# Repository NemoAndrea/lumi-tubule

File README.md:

> **warning** 🚧 Under Construction - There is still a lot of work to be done on this project. Have a look at issues if you want to contribute (e.g. review PCB) or check back later when the project is getting closer to release 👷

## LumiTubule - open hardware decorative led sculpture

LumiTubule is a simple decorative lamp in the shape of a [microtubule]() that can be programmed to respond to events (e.g. emails). While primarily decorative, the PCB comes with a temperature and humidity sensor and a basic accelerometer for user interaction - and a stemma QT port in case you want to add more sensors!

It's all powered by a small USB-C power supply, so it barely takes up any desk space.

The PCB design, 3D printable files and bill of materials are all available, so you can put together your own LumiTubule. If you would like to have one, but would rather not go through the assembly process, you can get in touch. 

### Components

There are 4 key components that make up the LumiTubule

1. The custom PCB with ESP32 microcontroller and onboard sensors
2. A [15W USB-C power supply](https://www.raspberrypi.com/products/type-c-power-supply/)
3. The 3D printed microtubule sculpture (translucent)
4. The 13 flexible LED filaments that sit inside the sculpture

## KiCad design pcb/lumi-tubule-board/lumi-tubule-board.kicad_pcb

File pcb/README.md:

### LumiTubule PCB

The LumiTubule PCB is generated with KiCad 6.0

The following plugins were used:

* [Teardrops plugin](https://github.com/NilujePerchut/kicad_scripts/tree/master/teardrops) (manual install - in PCBnew go to `tools` > `external plugins` > `open plugin directory`) 
* [Rounded tracks plugin](https://github.com/mitxela/kicad-round-tracks) (via plugin manager)

### Graphics

The graphics for the board are primarily created in Affinity Designer, with the help of [Inkscape](https://inkscape.org/) for some of the outline traces and image binarisation.

Some weird quirks during drawing process

- KiCad seems really picky about when it will render the hole in the board. The outline of the board has a lot of polygons. I am not sure what property of the inner circle makes it work better, but be aware that some frustrations may occur here if you try to change it.

### Considerations

> **Note** The points below provide some insight into why certain parts were selected. If you spot any errors in the calculations or reasoning, feel free to let me know!

**LED filament current setting resistor value `R_ext`**

The LED filaments can handle about 100mA current (more in practice seems fine), so let's aim for that value. We need to chose `R_ext` for the `TLC59108` and find an internal configuration to match. 

We look [in the datasheet](https://www.ti.com/lit/ds/symlink/tlc59108.pdf) and glance at section `10.1.1.2` ('adjusting the output current') . We see that the output current will depend on `R_ext`, `VG`, and `CM`. The latter two are configurable via internal register `IREF`. The default value of `CM` is 1, which sets `I_out/I_ref` = 15, and is listed as suitable for the 10mA-120mA regime; so we do not need to adjust this.   

`VG` is a more complicated value, being composed of the internal register value `HC` and `CC[5:0]`. Its default value is ~1 (0.992), which means that `V_ext` =1.25V (which has the following dependence: `V_ext = 1.26 * VG`).

Now we can put it together. We want `I_out`=100mA, so we need `I_ext` to be 100/15= 6.67mA. `I_ext` is simply set by `V_ext/R_ext`. So we need `R_ext` = 1.25/( 6.67 E-3) = **187.4 Ohm**. Dissipation in this resistor will only be (6.67mA)^2 * 187 = 10mW, so we can pretty much pick any package size.

### Generating fabrication outputs

We can generate a BOM from the schematic editor. We use a slightly modified version of [this custom script](https://gist.githubusercontent.com/arturo182/a8c4a4b96907cfccf616a1edb59d0389/raw/2c9191c0f1fe5471db3362ccf29f71d3235af4d4/bom2grouped_csv_jlcpcb.xsl) where we fetch part numbers from the custom field name 'JLCPCB ref' instead. You can see the value of this field in the schematic editor for each component. This is based on advice [from JLCPCB](https://support.jlcpcb.com/article/84-how-to-generate-the-bom-and-centroid-file-from-kicad).

We then turn to the PCB editor. We first need to run the [Rounded tracks plugin](https://github.com/mitxela/kicad-round-tracks). Run it with default parameters, and make sure you generate a new file. 

Next up, run the [Teardrops plugin](https://github.com/NilujePerchut/kicad_scripts/tree/master/teardrops). Use the following settings.

Now we can generate the `.gbr` files. We do this following [the suggestions by JLCPCB](https://support.jlcpcb.com/article/194-how-to-generate-gerber-and-drill-files-in-kicad-6). **In addition, we need to tick the place file origin option, as the PCB uses a virtual origin.** In short:

And for the drill file (we want to again pick the `drill/place file` origin:

Finally we need to generate the placement file. This is done from the PCB editor under `fabrication outputs`. We generate a `.pos` file. Per [instructions from JLCPCB](https://support.jlcpcb.com/article/84-how-to-generate-the-bom-and-centroid-file-from-kicad) we start with these settings in `KiCad`:

And then in the resulting `.csv` we change the following bits:

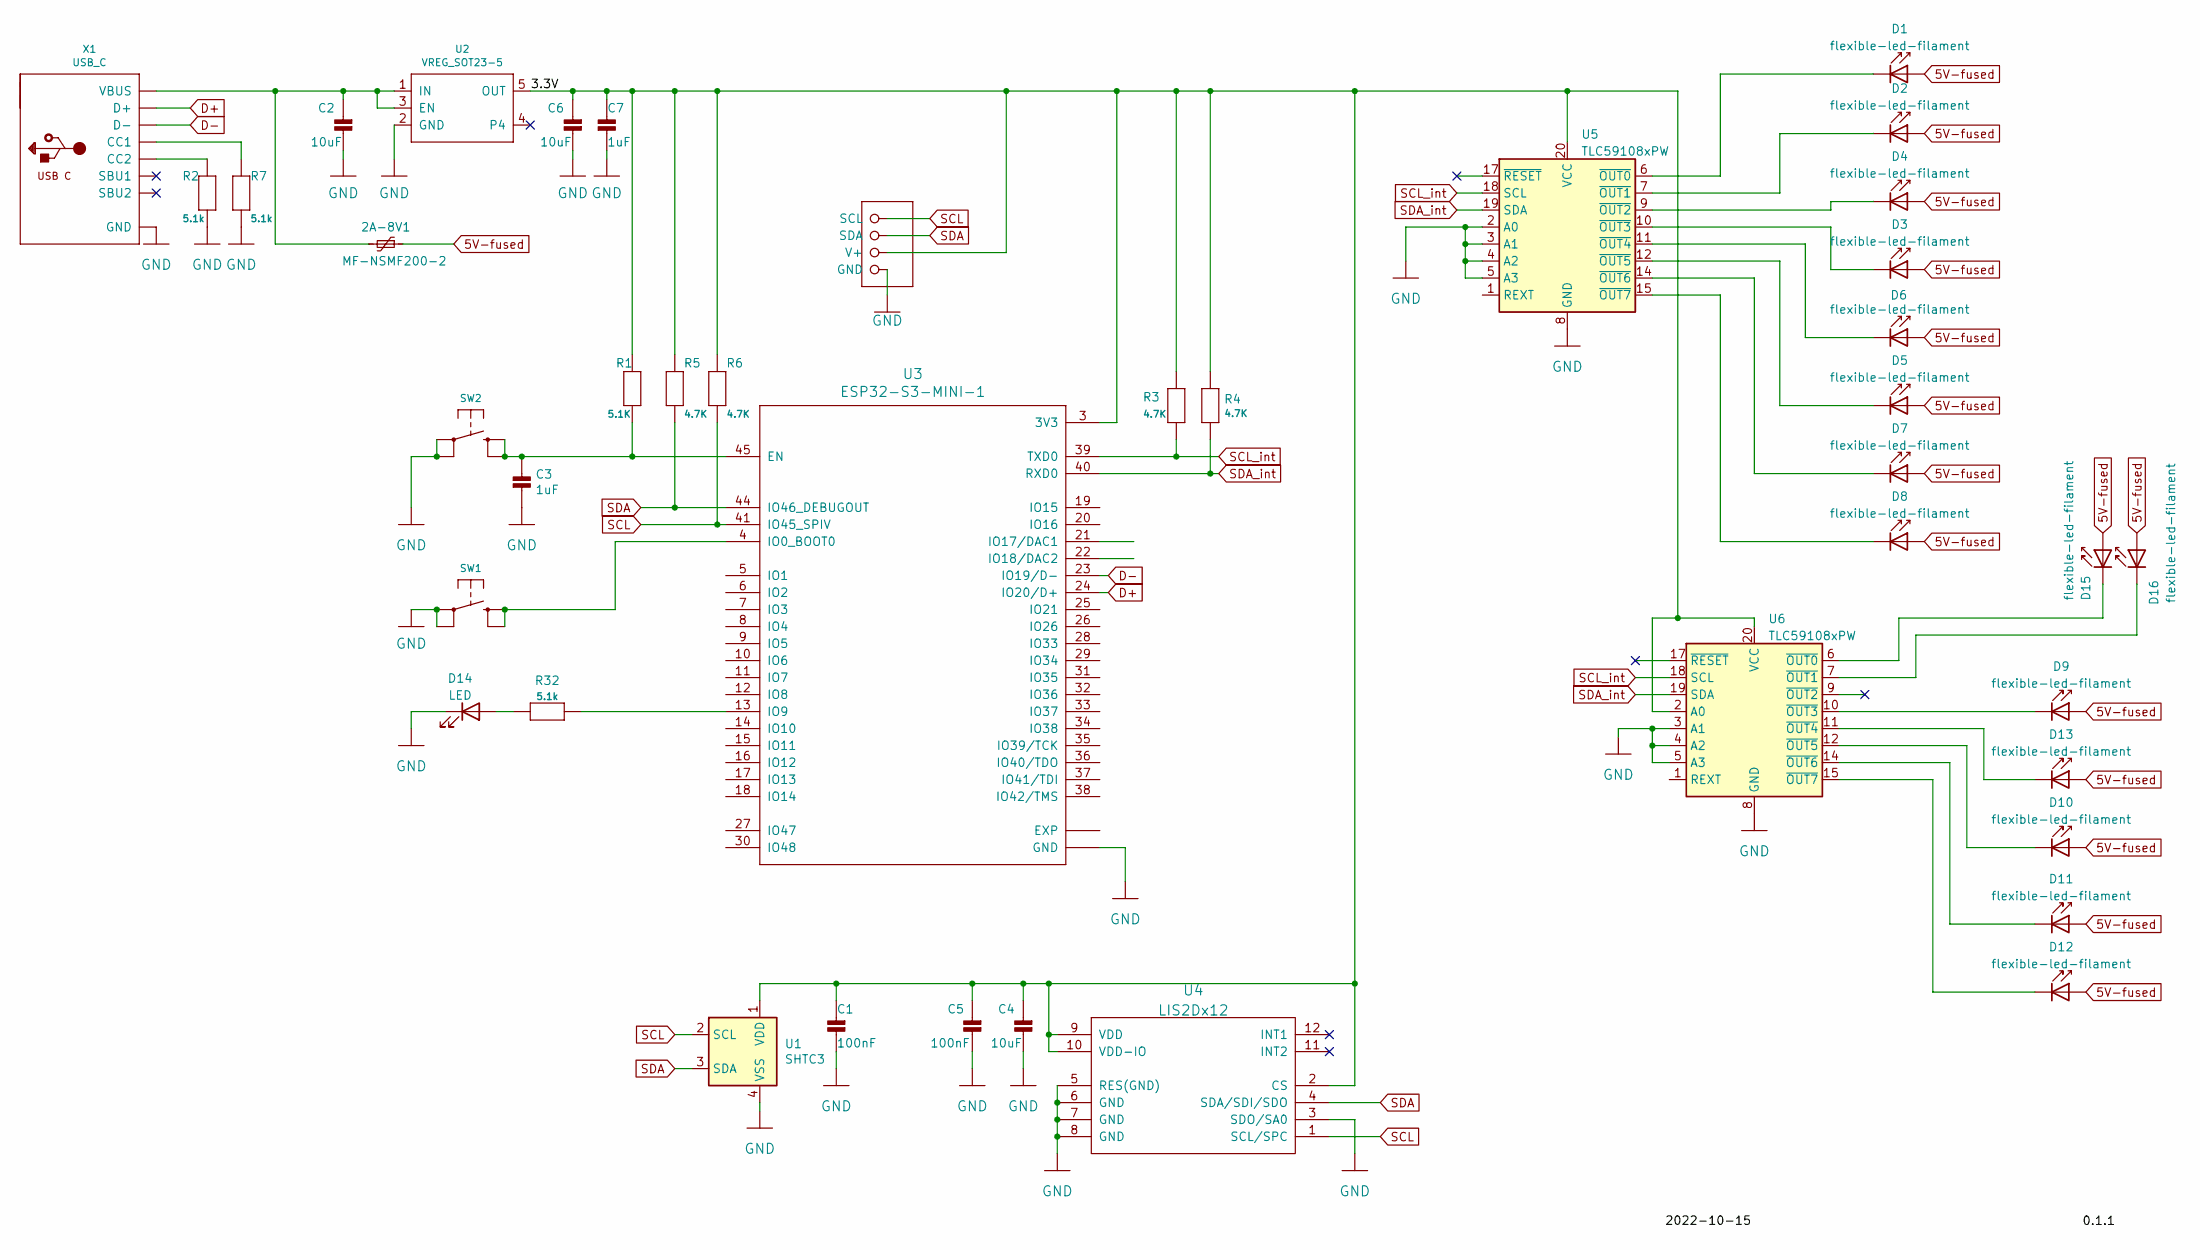
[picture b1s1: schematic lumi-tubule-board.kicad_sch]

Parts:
2A-8V1: MF-NSMF200-2
C1, C5: 100nF; C_0402_1005Metric; JLCPCB ref C307331
C2, C4, C6: 10uF; C_0805_2012Metric; JLCPCB ref C440198
C3, C7: 1uF; C_0603_1608Metric; JLCPCB ref C15849
CONN1: STEMMA_I2C_QTSKINNY; JST_SH_BM04B-SRSS-TB_1x04-1MP_P1.00mm_Vertical; JLCPCB ref C160390
D1, D2, D3, D4, D5, D6, D7, D8, D9, D10, D11, D12, D13, D15, D16: flexible-led-filament; Flexible LED filament viamount
D14: LED; LED_0603_1608Metric; JLCPCB ref C72043
R1: 5.1K; R_0805_2012Metric
R2, R7, R32: 5.1k; R_0603_1608Metric; JLCPCB ref C22961
R3, R4, R5, R6: 4.7K; R_0603_1608Metric; JLCPCB ref C23162
SW1, SW2: SWITCH_TACT_SMT4.6X2.8; BTN_KMR2_4.6X2.8
U1: SHTC3; Sensirion_DFN-4-1EP_2x2mm_P1mm_EP0.7x1.6mm; JLCPCB ref C194656
U2: VREG_SOT23-5; SOT-23-5; JLCPCB ref C176944
U3: ESP32-S3-MINI-1; ESP32-S2-MINI-1; JLCPCB ref C2913206
U4: LIS2Dx12; LGA-12_2x2mm_P0.5mm; JLCPCB ref C110926
U5, U6: TLC59108xPW; TSSOP-20_4.4x6.5mm_P0.65mm
X1: USB_C; USB_C_Receptacle_HRO_TYPE-C-31-M-12

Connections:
5V-fused: 2A-8V1.1, D1.2 (A), D2.2 (A), D3.2 (A), D4.2 (A), D5.2 (A), D6.2 (A), D7.2 (A), D8.2 (A), D9.2 (A), D10.2 (A), D11.2 (A), D12.2 (A), D13.2 (A), D15.2 (A), D16.2 (A)
/3.3V: C1.2, C4.2, C5.2, C6.2, C7.1, CONN1.2 (V+), R1.1, R3.1, R4.1, R5.1, R6.1, U1.1 (VDD), U2.5 (OUT), U3.3 (3V3), U4.2 (CS), U4.9 (VDD), U4.10 (VDD-IO), U5.20 (VCC), U6.2 (A0), U6.20 (VCC)
D+: U3.24 (IO20/D+), X1.A6 (D+), X1.B6 (D+)
D-: U3.23 (IO19/D-), X1.A7 (D-), X1.B7 (D-)
unnamed: 2A-8V1.2, C2.2, U2.1 (IN), U2.3 (EN), X1.A4 (VBUS), X1.A9 (VBUS), X1.B4 (VBUS), X1.B9 (VBUS)
unnamed: C3.1, R1.2, SW2.B (S), SW2.B' (S1), U3.45 (EN)
unnamed: D1.1 (K), U5.6 (~OUT0)
unnamed: D2.1 (K), U5.7 (~OUT1)
unnamed: D3.1 (K), U5.10 (~OUT3)
unnamed: D4.1 (K), U5.9 (~OUT2)
unnamed: D5.1 (K), U5.12 (~OUT5)
unnamed: D6.1 (K), U5.11 (~OUT4)
unnamed: D7.1 (K), U5.14 (~OUT6)
unnamed: D8.1 (K), U5.15 (~OUT7)
unnamed: D9.1 (K), U6.10 (~OUT3)
unnamed: D10.1 (K), U6.12 (~OUT5)
unnamed: D11.1 (K), U6.14 (~OUT6)
unnamed: D12.1 (K), U6.15 (~OUT7)
unnamed: D13.1 (K), U6.11 (~OUT4)
unnamed: D14.2 (A), R32.1
unnamed: D15.1 (K), U6.6 (~OUT0)
unnamed: D16.1 (K), U6.7 (~OUT1)
unnamed: R32.2, U3.13 (IO9)
unnamed: SW1.B (S), SW1.B' (S1), U3.4 (IO0_BOOT0)
unnamed: R7.1, X1.A5 (CC1)
unnamed: R2.1, X1.B5 (CC2)
SCL: CONN1.4 (SCL), R6.2, U1.2 (SCL), U3.41 (IO45_SPIV), U4.1 (SCL/SPC)
SCL_int: R3.2, U3.39 (TXD0), U5.18 (SCL), U6.18 (SCL)
SDA: CONN1.3 (SDA), R5.2, U1.3 (SDA), U3.44 (IO46_DEBUGOUT), U4.4 (SDA/SDI/SDO)
SDA_int: R4.2, U3.40 (RXD0), U5.19 (SDA), U6.19 (SDA)

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
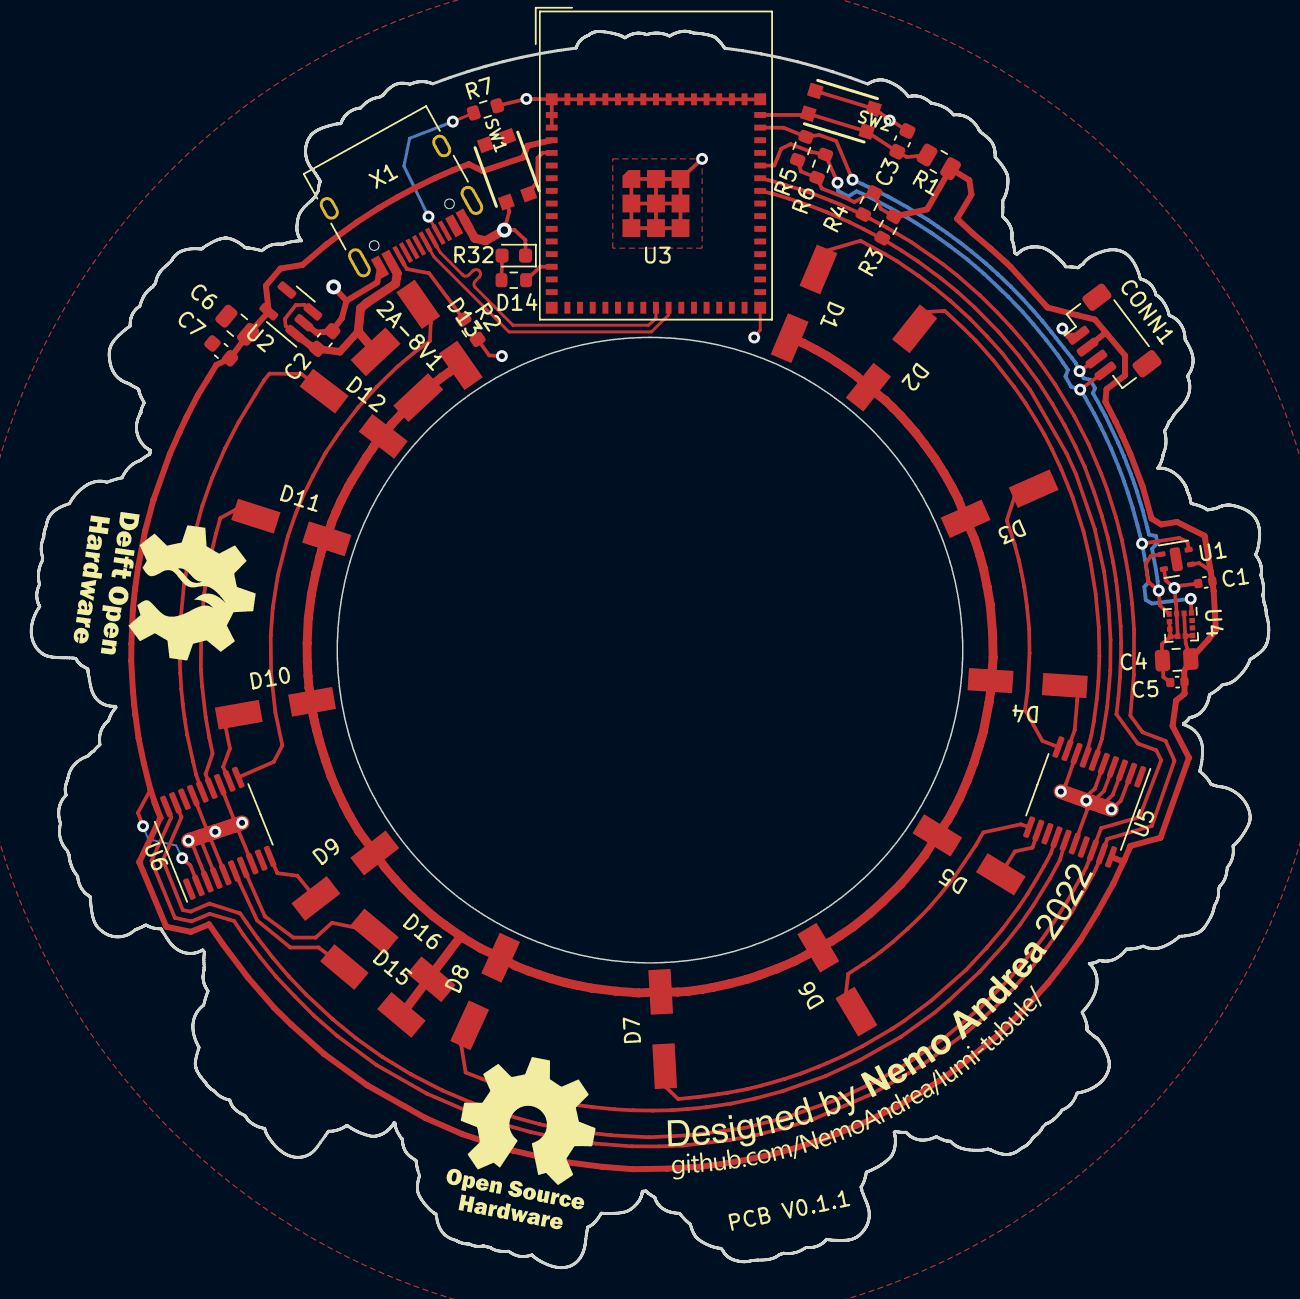
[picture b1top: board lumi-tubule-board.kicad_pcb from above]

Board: 2 copper layers, 83.1 x 83.0 mm, 42 parts (0 on the bottom side), 31 nets.

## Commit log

2022-09-20 Initial PCB version
    First version of kicad 6.0 PCB. All footprints loaded, but there are still some connection errors to be sorted out.
2022-09-20 Basic readme
    Spiced up the readme with banner image and basic explanation of the project
2022-09-23 Fix schematic footprint issues
    Fixed footprint errors in pcbnew. Initial exploration of layout. Fixed typo in banner.
2022-09-30 PCB design update
    Added LIS2DH12 accelerometer to PCB. Reworked the filament pads. Fixed footprints. Added pullup resistors to I2C lines. Started planning the layout in more compact footprint.
2022-10-01 First wiring for PCB
    First fully wired up arrangement for PCB. It's not pretty and the differential pairs are not good yet and the schematic still needs updating.
2022-10-13 Move to weakly reciprocal licence
    Move to CERN CERN-OHL-W and Mozilla Public License, v. 2.0 licences
2022-10-15 Revise PCB
    - fixed backwards USB port
    - redo power routing
    - make I2C lines cleaner
    - make differential lines length matched
2022-10-18 Add LED and fix pad numbers
    Add low power LED to board and fix some missing links between schematic and pcb design.
2022-10-22 Move to ground plane approach
    Opt to go for ground plane design and forgo extra PCB art colour. Simplifies a lot of things. Currently I2C lines still need to be wired up and some traced cleaned up.
2022-10-23 Correct and complete traces
    Redid ugly traces and connected SDA/SCL lines to new ground plane design.
2022-11-01 Fix MOSFET wiring
    Fixed the MOSFETs' wiring, which was all wrong. Rerouted mosfet out via ground plane, freeing up space for the Vsup line on top of board. Removed the diagnosis LED line on the back of PCB which was i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
2022-11-03 Add board graphics
    Added main backside graphics as well as open hardware logos and metadata text
2022-11-03 Fix some DRC violations
2023-02-13 Rough layout with TLC59108
    Made rough layout with the TLC59108 LED drivers (2 on the board). Routing is now a lot easier. Still some minor issues to be ironed out. Schematic is complete; PCB layout still needs routing work.
2023-02-18 Complete TLC59018 implementaiton
    Fully routed board which should theoretically need only cosmetic alterations. Some issues with soldermask goign outside the board (might cause manufacturer to get upset).
2023-02-18 Fix outdated readme
2023-02-18 Add current settings resistors to TLC59108
    Add 187ohm resistors to set current tartget on TLC59108
2023-02-18 Add USB data/power splitter board
    Add a small separate (mousebites) USB power/data splitter board. Fits neatly within the central cutout of the main board.
2023-02-19 Finalise fabrication output
    Minor changes, fixes to BOM and schematic footprints.
2023-03-13 Fix fuse footprint
2023-03-13 Produced PCB files
    PCB version 0.1.1 files. Corrected one error in production regarding voltage regulator.
2023-03-13 Update fabrication ouput setting documentation
    Information on how to turn kicad files into JLCPCB production outputs.
2023-03-13 Remove old kicad 5.0 file
2023-03-13 Remove garbage files
2023-04-01 PCB V0.1.2
    Fixed some big issues with the USB type-C connector traces. Annotated all the nets so PCB is easier to follow. Still strange issue with fills in the buddy USB board.
